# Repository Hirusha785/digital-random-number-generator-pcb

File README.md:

# 🎲 Digital Random Number Generator PCB

A custom-designed **Digital Random Number Generator PCB** developed using **KiCad**.  
This project uses an 8051-family microcontroller, dual seven-segment displays, 74LS48 BCD-to-seven-segment display driver ICs, push-button controls, and a regulated 5V logic power supply to generate and display random numbers.

---

## 📌 Project Overview

The **Digital Random Number Generator PCB** is a digital electronics and embedded hardware project designed to generate and display random numbers using two seven-segment displays.

The circuit is built around an **8051-family microcontroller**, which handles the random number generation logic. The generated number is separated into two BCD digits and sent to two **74LS48 BCD-to-seven-segment decoder/driver ICs**. Each driver IC then controls one seven-segment display.

This project demonstrates the complete PCB design workflow in KiCad, including schematic design, component footprint assignment, PCB layout, routing, silkscreen labeling, 3D visualization, and preparation for fabrication.

---

## ✨ Key Features

- Microcontroller-based random number generation
- Dual seven-segment display output
- 74LS48 BCD-to-seven-segment decoder/driver ICs
- Push-button input for number generation
- Dedicated reset/control button
- 5V DC logic power input
- Crystal oscillator circuit for microcontroller clock generation
- Current-limiting resistors for display protection
- Organized schematic sections for power, control, and display output
- Compact PCB layout with mounting holes
- Complete KiCad schematic, PCB layout, and 3D PCB preview

---

## 🧠 System Architecture

```txt
Push Button Input
        ↓
8051 Microcontroller
        ↓
Random Number Generation Logic
        ↓
BCD Output Signals
        ↓
74LS48 Display Driver ICs
        ↓
Dual Seven-Segment Displays
```

---

## ⚙️ Hardware Description

The PCB is divided into three main sections:

1. **Power Supply Section**
2. **Random Number Generation Control Section**
3. **Display Driver and Seven-Segment Output Section**

The user presses the push button to trigger the random number generation process. The microcontroller generates a random value and sends the corresponding BCD output signals to the display driver ICs. The 74LS48 ICs decode the BCD signals and drive the seven-segment displays.

---

## 🧩 Main Components

| Component | Description |
|---|---|
| 8051 Microcontroller | Main control unit used for random number generation |
| 74LS48 IC | BCD-to-seven-segment decoder/driver |
| Seven-Segment Displays | Displays the generated random number |
| Push Buttons | Used for reset and random number generation control |
| Crystal Oscillator | Provides the clock signal for the microcontroller |
| Capacitors | Used for oscillator stability, reset timing, and filtering |
| Resistors | Used for current limiting and pull-up/pull-down functions |
| Screw Terminal | Provides external 5V power input |
| PCB | Custom-designed printed circuit board created using KiCad |

---

## ⚡ Power Supply

The circuit is designed to operate using a regulated **5V DC power supply**.

Power is supplied through a screw terminal connector.

```txt
+5V  → VCC
GND  → Ground
```

> ⚠️ Always verify the power polarity before powering the PCB.

---

## 🔢 Display Driver Section

The display section uses two **74LS48 BCD-to-seven-segment decoder/driver ICs**.

Each display driver receives a 4-bit BCD input from the microcontroller and controls one seven-segment display. Current-limiting resistors are used to protect the display segments.

The display section includes:

- Two seven-segment displays
- Two 74LS48 display driver ICs
- Segment current-limiting resistors
- BCD signal routing from the microcontroller
- Seven-segment output routing to the displays

---

## 🎛️ Control Section

The control section contains the main microcontroller circuit and supporting components.

It includes:

- 8051-family microcontroller
- Push-button input
- Reset button
- Crystal oscillator circuit
- Oscillator capacitors
- Reset capacitor
- Pull-up/pull-down resistors

The microcontroller manages the random number generation process and sends the correct BCD values to the display driver section.

---

## 🖥️ PCB Design

The PCB was designed using **KiCad** and includes:

- Schematic capture
- Footprint assignment
- PCB layout design
- Manual routing
- Silkscreen labeling
- Mounting holes
- 3D PCB visualization
- Fabrication-ready design structure

The board layout is organized to clearly separate the power input, microcontroller control section, and display output section.

---

## 📷 PCB Preview

The project includes the following design previews:

### Schematic

### PCB Layout

### 3D View

---

## 🚀 Applications

This PCB can be used for:

- Digital electronics learning
- Embedded systems practice
- Microcontroller-based hardware design
- Seven-segment display driver testing
- Random number display applications
- KiCad PCB design portfolio development
- Basic digital logic demonstration projects

---

## ✅ Project Status

| Section | Status |
|---|---|
| Schematic Design | Completed |
| PCB Layout | Completed |
| 3D PCB Preview | Completed |
| Gerber File Export | Ready / To be generated |
| Hardware Testing | Pending |

---

## 👨‍💻 Author

**Fernando S.M.H.G.**

---

## 📜 License

This project is licensed under the **MIT License**.

You are free to use, modify, and distribute this project for educational, personal, and development purposes, provided that the original license terms are followed.

See the `LICENSE` file for more details.

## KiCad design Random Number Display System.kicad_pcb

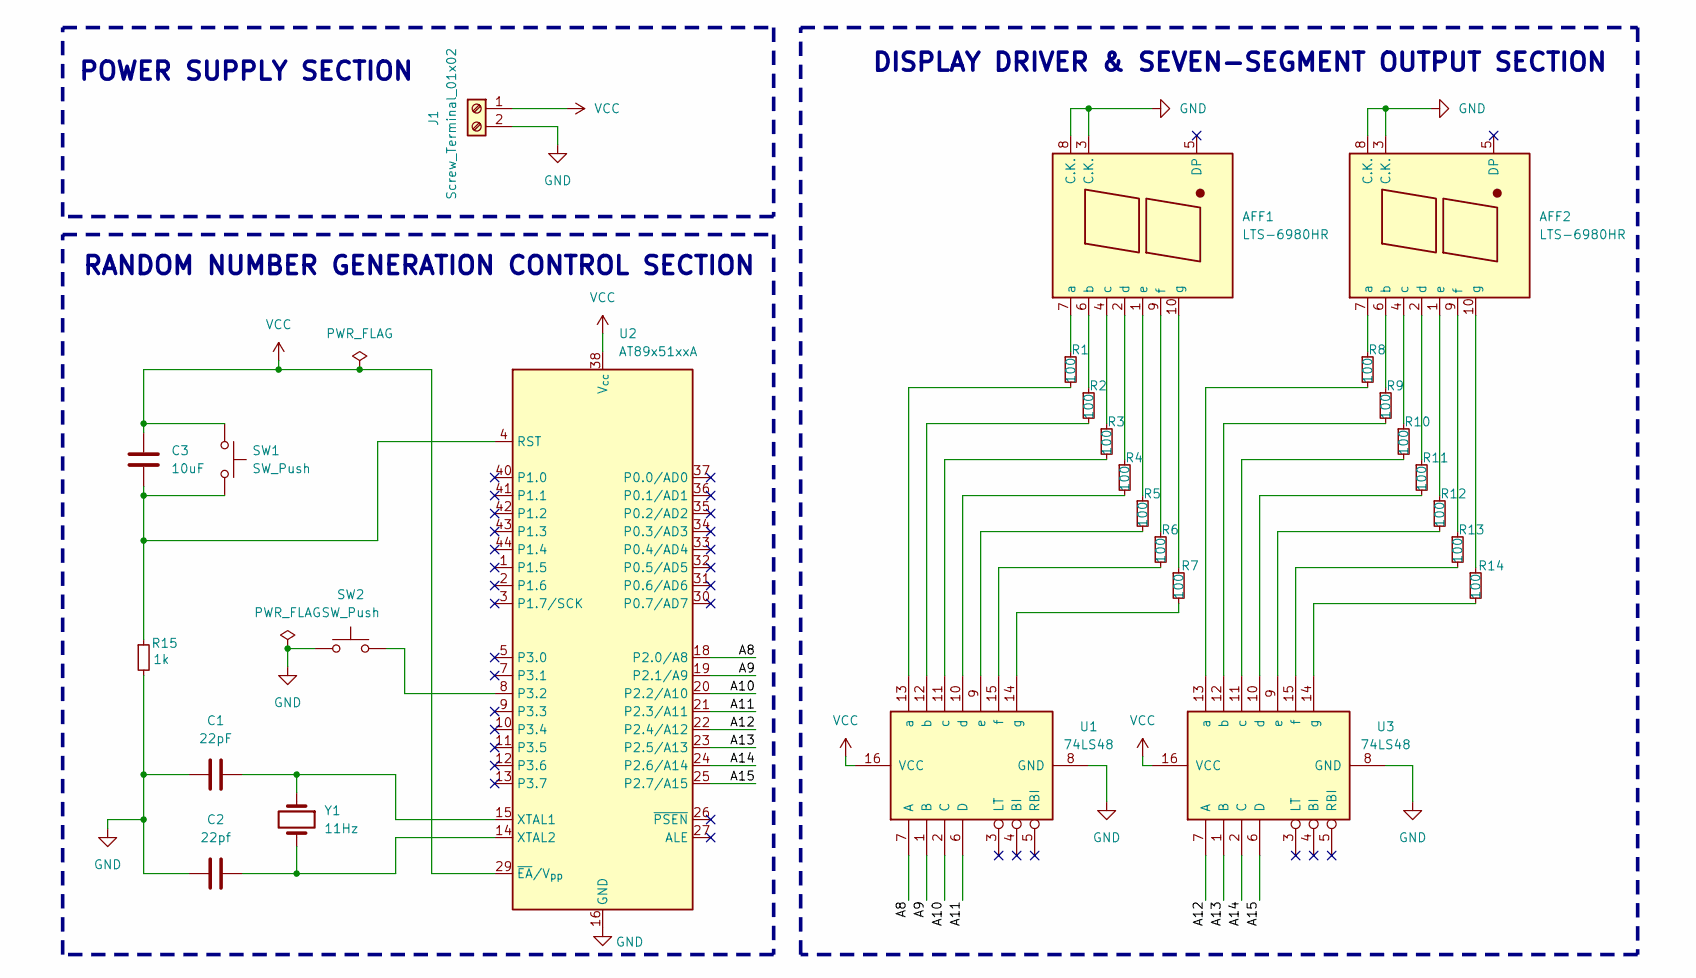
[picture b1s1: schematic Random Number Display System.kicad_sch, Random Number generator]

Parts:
AFF1, AFF2: LTS-6980HR; 7SegmentLED_LTS6760_LTS6780
C1: 22pF; C_1206_3216Metric
C2: 22pf; C_1206_3216Metric
C3: 10uF; C_1206_3216Metric
J1: Screw_Terminal_01x02; TerminalBlock_bornier-2_P5.08mm
R1, R2, R3, R4, R5, R6, R7, R8, R9, R10, R11, R12, R13, R14: 100; R_1206_3216Metric
R15: 1k; R_1206_3216Metric
SW1, SW2: SW_Push; SW_PUSH_6mm_H4.3mm
U1, U3: 74LS48; DIP787W45P254L927H533Q8
U2: AT89x51xxA; TQFP-44_10x10mm_P0.8mm
Y1: 11Hz; Crystal_SMD_0603-2Pin_6.0x3.5mm

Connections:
/A8: U1.7 (A), U2.18 (P2.0/A8)
/A9: U1.1 (B), U2.19 (P2.1/A9)
/A10: U1.2 (C), U2.20 (P2.2/A10)
/A11: U1.6 (D), U2.21 (P2.3/A11)
/A12: U2.22 (P2.4/A12), U3.7 (A)
/A13: U2.23 (P2.5/A13), U3.1 (B)
/A14: U2.24 (P2.6/A14), U3.2 (C)
/A15: U2.25 (P2.7/A15), U3.6 (D)
GND: AFF1.3 (C.K.), AFF1.8 (C.K.), AFF2.3 (C.K.), AFF2.8 (C.K.), C1.1, C2.1, J1.2, R15.2, SW2.1, U1.8 (GND), U2.16 (GND), U2.17 (GND), U3.8 (GND)
unnamed: AFF1.7 (a), R1.1
unnamed: AFF1.6 (b), R2.1
unnamed: AFF1.4 (c), R3.1
unnamed: AFF1.2 (d), R4.1
unnamed: AFF1.1 (e), R5.1
unnamed: AFF1.9 (f), R6.1
unnamed: AFF1.10 (g), R7.1
unnamed: AFF2.7 (a), R8.1
unnamed: AFF2.6 (b), R9.1
unnamed: AFF2.4 (c), R10.1
unnamed: AFF2.2 (d), R11.1
unnamed: AFF2.1 (e), R12.1
unnamed: AFF2.9 (f), R13.1
unnamed: AFF2.10 (g), R14.1
unnamed: R1.2, U1.13 (a)
unnamed: R2.2, U1.12 (b)
unnamed: R3.2, U1.11 (c)
unnamed: R4.2, U1.10 (d)
unnamed: R5.2, U1.9 (e)
unnamed: R6.2, U1.15 (f)
unnamed: R7.2, U1.14 (g)
unnamed: SW2.2, U2.8 (P3.2)
unnamed: C3.2, R15.1, SW1.2, U2.4 (RST)
unnamed: C1.2, U2.15 (XTAL1), Y1.1
unnamed: C2.2, U2.14 (XTAL2), Y1.2
unnamed: R8.2, U3.13 (a)
unnamed: R9.2, U3.12 (b)
unnamed: R10.2, U3.11 (c)
unnamed: R11.2, U3.10 (d)
unnamed: R12.2, U3.9 (e)
unnamed: R13.2, U3.15 (f)
unnamed: R14.2, U3.14 (g)
VCC: C3.1, J1.1, SW1.1, U1.16 (VCC), U2.29 (~EA/V_{pp}), U2.38 (V_{cc}), U3.16 (VCC)

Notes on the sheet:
POWER SUPPLY SECTION
DISPLAY DRIVER & SEVEN-SEGMENT OUTPUT SECTION
RANDOM NUMBER GENERATION CONTROL SECTION

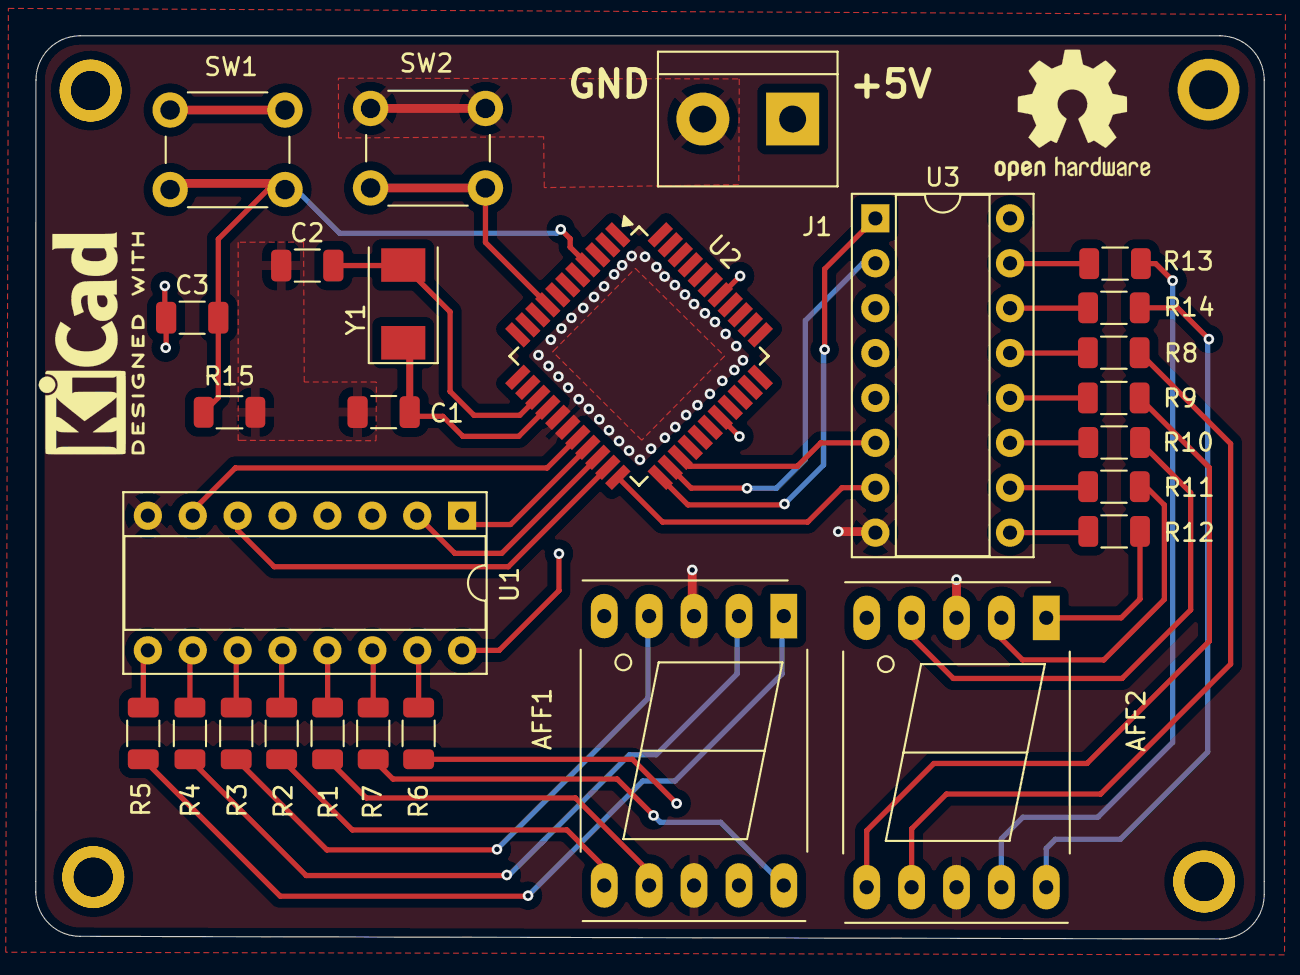
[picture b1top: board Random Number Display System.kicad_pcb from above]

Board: 4 copper layers, 69.5 x 51.1 mm, 27 parts (0 on the bottom side), 42 nets.

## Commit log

2026-06-08 Revise README for Digital Random Number Generator PCB
    Updated README to enhance project description, features, and structure.

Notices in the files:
README.md:
License: MIT
